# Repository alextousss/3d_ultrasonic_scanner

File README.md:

### An Ultrasonic 3D Scanner

Detailed build log and infos [on my website](http://alextoussaint.com/2021-04-28_How-I-built-an-ultrasonic-3d-scanner.html) 

If you're looking for instructions detailed enough to build it for yourself, just add an Issue and I'll do it.
I also haven't had the time to make the code human-readable. Though, it's still understandable.

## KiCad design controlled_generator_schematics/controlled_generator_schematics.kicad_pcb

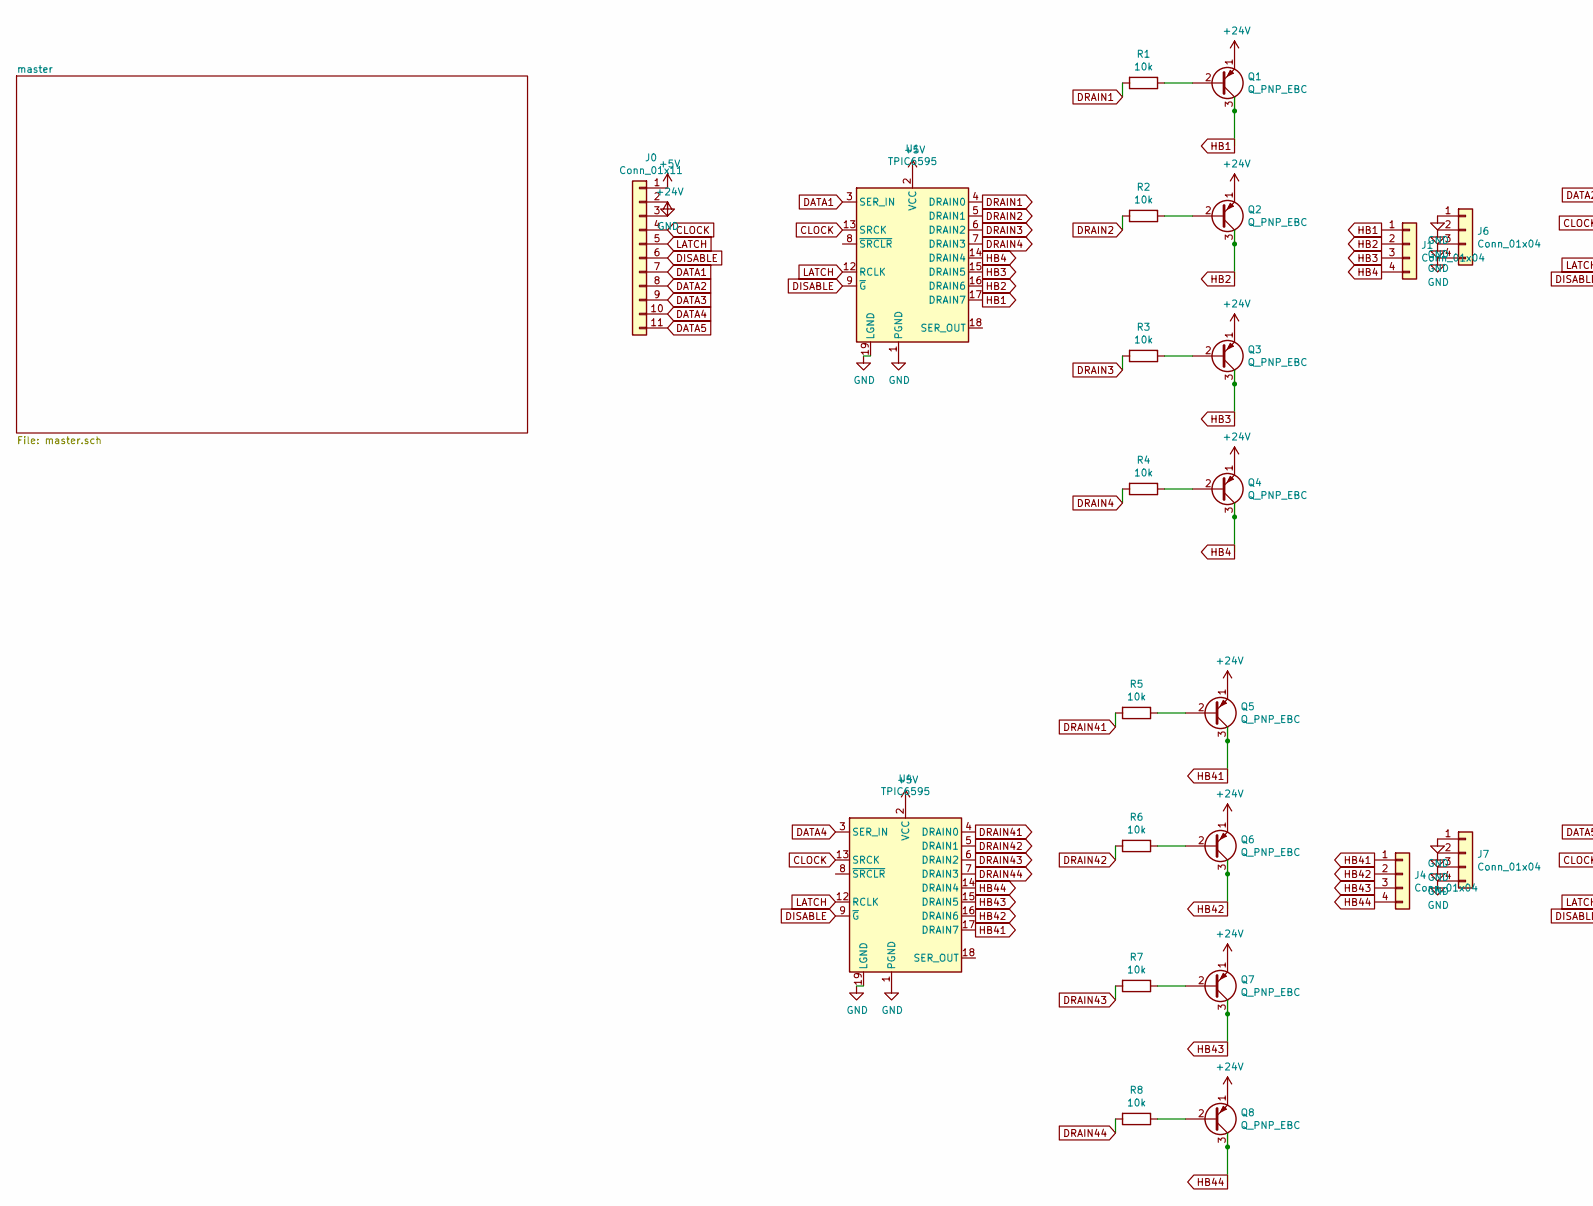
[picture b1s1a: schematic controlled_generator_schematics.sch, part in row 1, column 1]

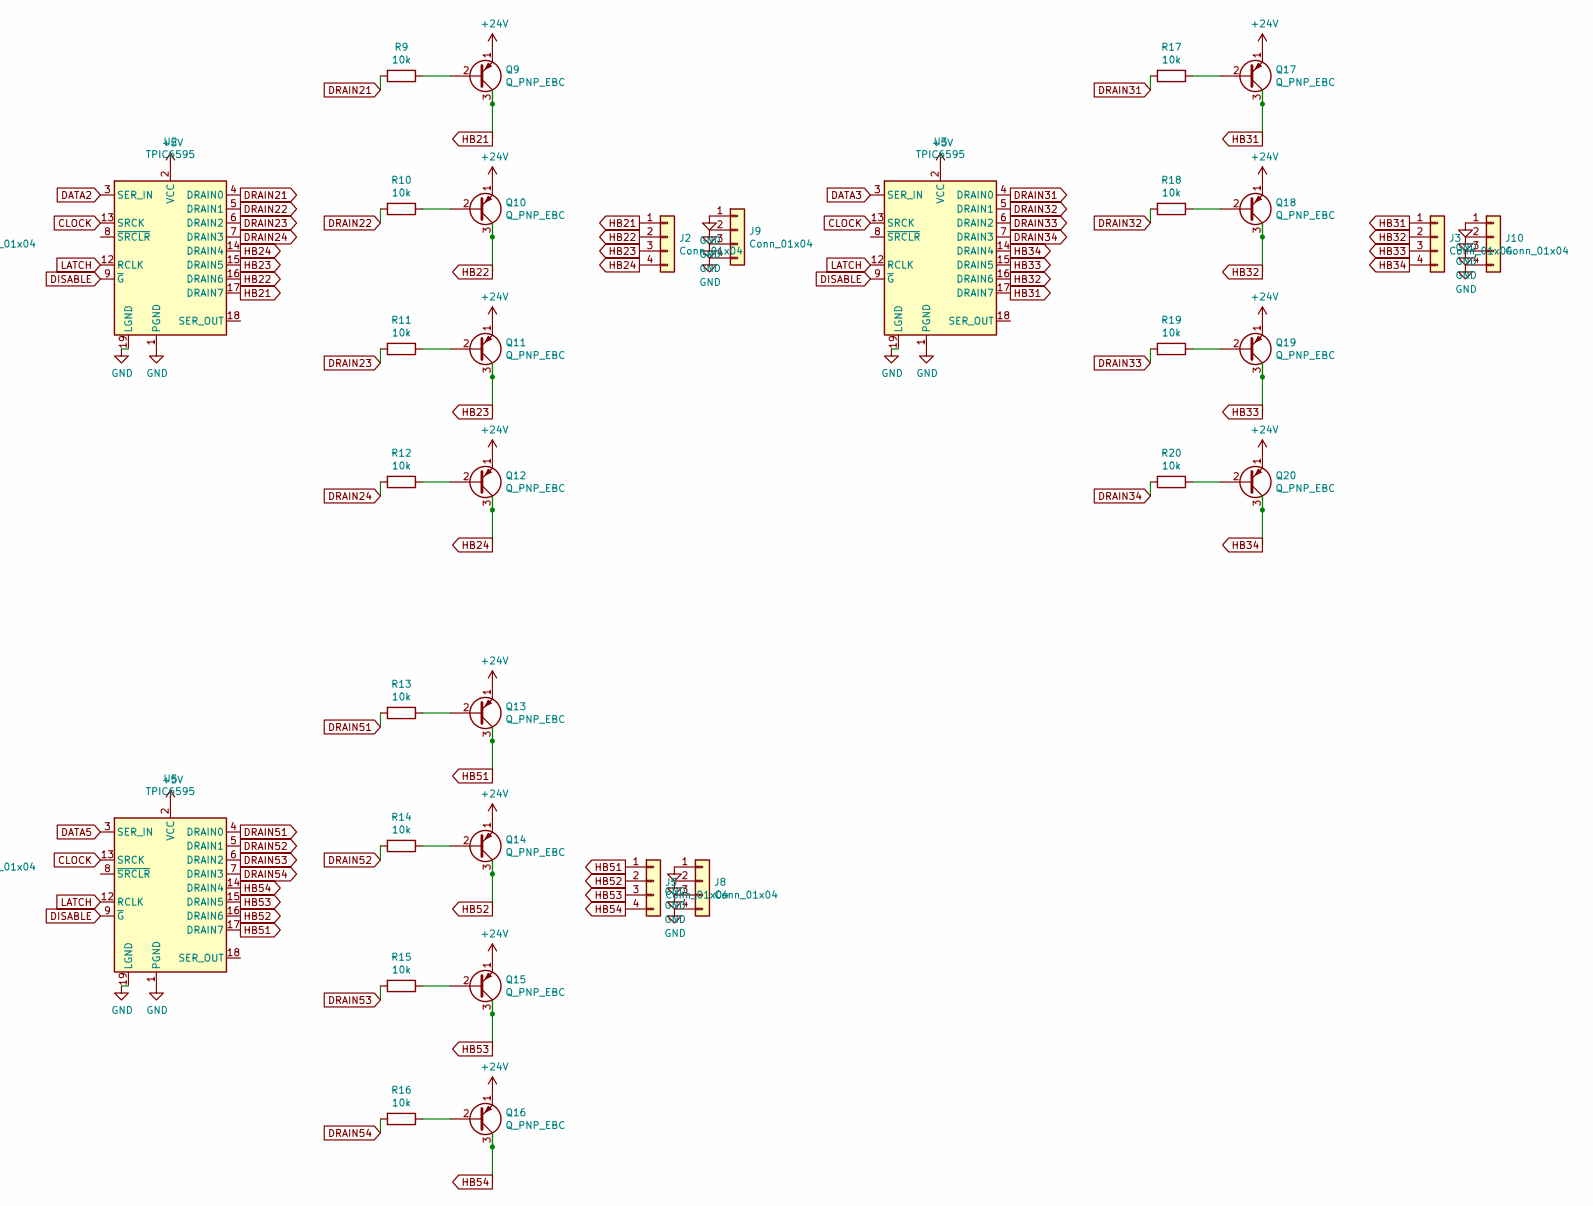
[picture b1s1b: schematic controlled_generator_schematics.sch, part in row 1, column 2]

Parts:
J0: Conn_01x11; PinHeader_1x11_P2.54mm_Horizontal
J1, J2, J3, J4, J5, J6, J7, J8, J9, J10: Conn_01x04; PinHeader_1x04_P2.54mm_Vertical
Q1, Q2, Q3, Q4, Q5, Q6, Q7, Q8, Q9, Q10, Q11, Q12, Q13, Q14, Q15, Q16, Q17, Q18, Q19, Q20: Q_PNP_EBC; TO-92
R1, R2, R3, R4, R5, R6, R7, R8, R9, R10, R11, R12, R13, R14, R15, R16, R17, R18, R19, R20: 10k; R_Axial_DIN0204_L3.6mm_D1.6mm_P2.54mm_Vertical
U1, U2, U3, U4, U5: TPIC6595; DIP-20_W7.62mm_Socket

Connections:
+5V: J0.1, U1.2 (VCC), U2.2 (VCC), U3.2 (VCC), U4.2 (VCC), U5.2 (VCC)
+24V: J0.3, Q1.1 (E), Q2.1 (E), Q3.1 (E), Q4.1 (E), Q5.1 (E), Q6.1 (E), Q7.1 (E), Q8.1 (E), Q9.1 (E), Q10.1 (E), Q11.1 (E), Q12.1 (E), Q13.1 (E), Q14.1 (E), Q15.1 (E), Q16.1 (E), Q17.1 (E), Q18.1 (E), Q19.1 (E), Q20.1 (E)
CLOCK: J0.4, U1.13 (SRCK), U2.13 (SRCK), U3.13 (SRCK), U4.13 (SRCK), U5.13 (SRCK)
DATA1: J0.7, U1.3 (SER_IN)
DATA2: J0.8, U2.3 (SER_IN)
DATA3: J0.9, U3.3 (SER_IN)
DATA4: J0.10, U4.3 (SER_IN)
DATA5: J0.11, U5.3 (SER_IN)
DISABLE: J0.6, U1.9 (~G), U2.9 (~G), U3.9 (~G), U4.9 (~G), U5.9 (~G)
DRAIN1: R1.2, U1.4 (DRAIN0)
DRAIN2: R2.2, U1.5 (DRAIN1)
DRAIN3: R3.2, U1.6 (DRAIN2)
DRAIN4: R4.2, U1.7 (DRAIN3)
DRAIN21: R9.2, U2.4 (DRAIN0)
DRAIN22: R10.2, U2.5 (DRAIN1)
DRAIN23: R11.2, U2.6 (DRAIN2)
DRAIN24: R12.2, U2.7 (DRAIN3)
DRAIN31: R17.2, U3.4 (DRAIN0)
DRAIN32: R18.2, U3.5 (DRAIN1)
DRAIN33: R19.2, U3.6 (DRAIN2)
DRAIN34: R20.2, U3.7 (DRAIN3)
DRAIN41: R5.2, U4.4 (DRAIN0)
DRAIN42: R6.2, U4.5 (DRAIN1)
DRAIN43: R7.2, U4.6 (DRAIN2)
DRAIN44: R8.2, U4.7 (DRAIN3)
DRAIN51: R13.2, U5.4 (DRAIN0)
DRAIN52: R14.2, U5.5 (DRAIN1)
DRAIN53: R15.2, U5.6 (DRAIN2)
DRAIN54: R16.2, U5.7 (DRAIN3)
GND: J0.2, J6.1, J6.2, J6.3, J6.4, J7.1, J7.2, J7.3, J7.4, J8.1, J8.2, J8.3, J8.4, J9.1, J9.2, J9.3, J9.4, J10.1, J10.2, J10.3, J10.4, U1.1 (PGND), U1.10 (PGND), U1.11 (PGND), U1.19 (LGND), U1.20 (PGND), U2.1 (PGND), U2.10 (PGND), U2.11 (PGND), U2.19 (LGND), U2.20 (PGND), U3.1 (PGND), U3.10 (PGND), U3.11 (PGND), U3.19 (LGND), U3.20 (PGND), U4.1 (PGND), U4.10 (PGND), U4.11 (PGND), U4.19 (LGND), U4.20 (PGND), U5.1 (PGND), U5.10 (PGND), U5.11 (PGND), U5.19 (LGND), U5.20 (PGND)
HB1: J1.1, Q1.3 (C), U1.17 (DRAIN7)
HB2: J1.2, Q2.3 (C), U1.16 (DRAIN6)
HB3: J1.3, Q3.3 (C), U1.15 (DRAIN5)
HB4: J1.4, Q4.3 (C), U1.14 (DRAIN4)
HB21: J2.1, Q9.3 (C), U2.17 (DRAIN7)
HB22: J2.2, Q10.3 (C), U2.16 (DRAIN6)
HB23: J2.3, Q11.3 (C), U2.15 (DRAIN5)
HB24: J2.4, Q12.3 (C), U2.14 (DRAIN4)
HB31: J3.1, Q17.3 (C), U3.17 (DRAIN7)
HB32: J3.2, Q18.3 (C), U3.16 (DRAIN6)
HB33: J3.3, Q19.3 (C), U3.15 (DRAIN5)
HB34: J3.4, Q20.3 (C), U3.14 (DRAIN4)
HB41: J4.1, Q5.3 (C), U4.17 (DRAIN7)
HB42: J4.2, Q6.3 (C), U4.16 (DRAIN6)
HB43: J4.3, Q7.3 (C), U4.15 (DRAIN5)
HB44: J4.4, Q8.3 (C), U4.14 (DRAIN4)
HB51: J5.1, Q13.3 (C), U5.17 (DRAIN7)
HB52: J5.2, Q14.3 (C), U5.16 (DRAIN6)
HB53: J5.3, Q15.3 (C), U5.15 (DRAIN5)
HB54: J5.4, Q16.3 (C), U5.14 (DRAIN4)
LATCH: J0.5, U1.12 (RCLK), U2.12 (RCLK), U3.12 (RCLK), U4.12 (RCLK), U5.12 (RCLK)
unnamed: Q1.2 (B), R1.1
unnamed: Q2.2 (B), R2.1
unnamed: Q3.2 (B), R3.1
unnamed: Q4.2 (B), R4.1
unnamed: Q5.2 (B), R5.1
unnamed: Q6.2 (B), R6.1
unnamed: Q7.2 (B), R7.1
unnamed: Q8.2 (B), R8.1
unnamed: Q9.2 (B), R9.1
unnamed: Q10.2 (B), R10.1
unnamed: Q11.2 (B), R11.1
unnamed: Q12.2 (B), R12.1
unnamed: Q13.2 (B), R13.1
unnamed: Q14.2 (B), R14.1
unnamed: Q15.2 (B), R15.1
unnamed: Q16.2 (B), R16.1
unnamed: Q17.2 (B), R17.1
unnamed: Q18.2 (B), R18.1
unnamed: Q19.2 (B), R19.1
unnamed: Q20.2 (B), R20.1

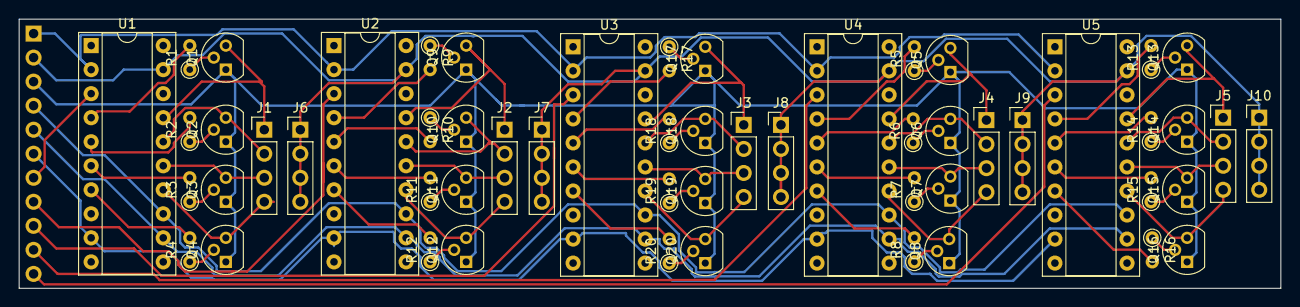
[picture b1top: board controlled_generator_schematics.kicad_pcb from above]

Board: 2 copper layers, 133.4 x 28.4 mm, 56 parts (1 on the bottom side), 71 nets.

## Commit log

2021-06-05 Create LICENSE
